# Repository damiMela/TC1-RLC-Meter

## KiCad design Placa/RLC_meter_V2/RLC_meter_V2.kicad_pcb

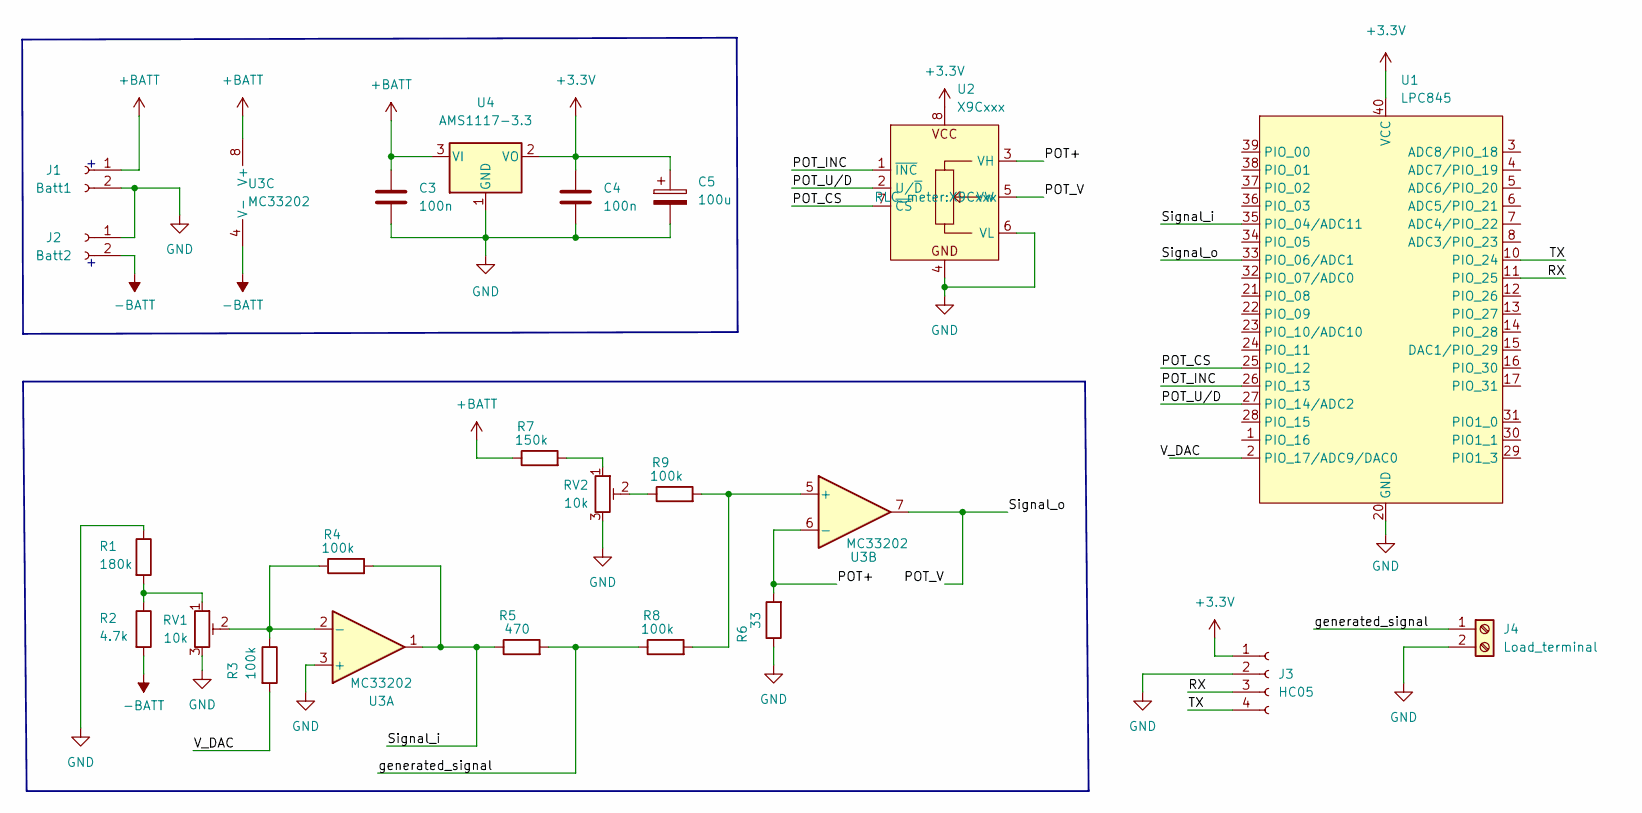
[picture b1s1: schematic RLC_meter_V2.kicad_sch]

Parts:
C3, C4: 100n; C_Disc_D5.0mm_W2.5mm_P2.50mm
C5: 100u; CP_Radial_D8.0mm_P5.00mm
J1: Batt1; PinHeader_1x02_P2.54mm_Vertical
J2: Batt2; PinHeader_1x02_P2.54mm_Vertical
J3: HC05; PinHeader_1x04_P2.54mm_Horizontal
J4: Load_terminal; TerminalBlock_Philmore_TB132_1x02_P5.00mm_Horizontal
R1: 180k; R_Axial_DIN0207_L6.3mm_D2.5mm_P15.24mm_Horizontal
R2: 4.7k; R_Axial_DIN0207_L6.3mm_D2.5mm_P15.24mm_Horizontal
R3, R4, R8, R9: 100k; R_Axial_DIN0207_L6.3mm_D2.5mm_P15.24mm_Horizontal
R5: 470; R_Axial_DIN0207_L6.3mm_D2.5mm_P15.24mm_Horizontal
R6: 33; R_Axial_DIN0207_L6.3mm_D2.5mm_P15.24mm_Horizontal
R7: 150k; R_Axial_DIN0207_L6.3mm_D2.5mm_P15.24mm_Horizontal
RV1, RV2: 10k; Potentiometer_Bourns_3386C_Horizontal
U1: LPC845
U2: X9Cxxx
U3: MC33202; DIP-8_W7.62mm_Socket_LongPads
U4: AMS1117-3.3; PinHeader_1x03_P2.54mm_Vertical

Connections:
+3.3V: C4.1, C5.1, J3.1, U1.40 (VCC), U2.8, U4.2 (VO)
+BATT: C3.1, J1.1, R7.1, U3.8 (V+), U4.3 (VI)
-BATT: J2.2, R2.2, U3.4 (V-)
/POT+: R6.2, U2.3 (VH), U3.6 (-)
/POT_CS: U1.25 (PIO_12), U2.7 (~CS)
/POT_INC: U1.26 (PIO_13), U2.1 (~INC)
/POT_U/D: U1.27 (PIO_14/ADC2), U2.2 (U/~D)
/POT_V: U1.33 (PIO_06/ADC1), U2.5 (VW), U3.7
/RX: J3.3, U1.11 (PIO_25)
/Signal_i: R4.2, R5.1, U1.35 (PIO_04/ADC11), U3.1
/TX: J3.4, U1.10 (PIO_24)
/V_DAC: R3.2, U1.2 (PIO_17/ADC9/DAC0)
/generated_signal: J4.1, R5.2, R8.1
GND: C3.2, C4.2, C5.2, J1.2, J2.1, J3.2, J4.2, R1.1, R6.1, RV1.3, RV2.3, U1.20 (GND), U2.4, U2.6 (VL), U3.3 (+), U4.1 (GND)
unnamed: R1.2, R2.1, RV1.1
unnamed: R3.1, R4.1, RV1.2, U3.2 (-)
unnamed: R7.2, RV2.1
unnamed: R9.1, RV2.2
unnamed: R8.2, R9.2, U3.5 (+)

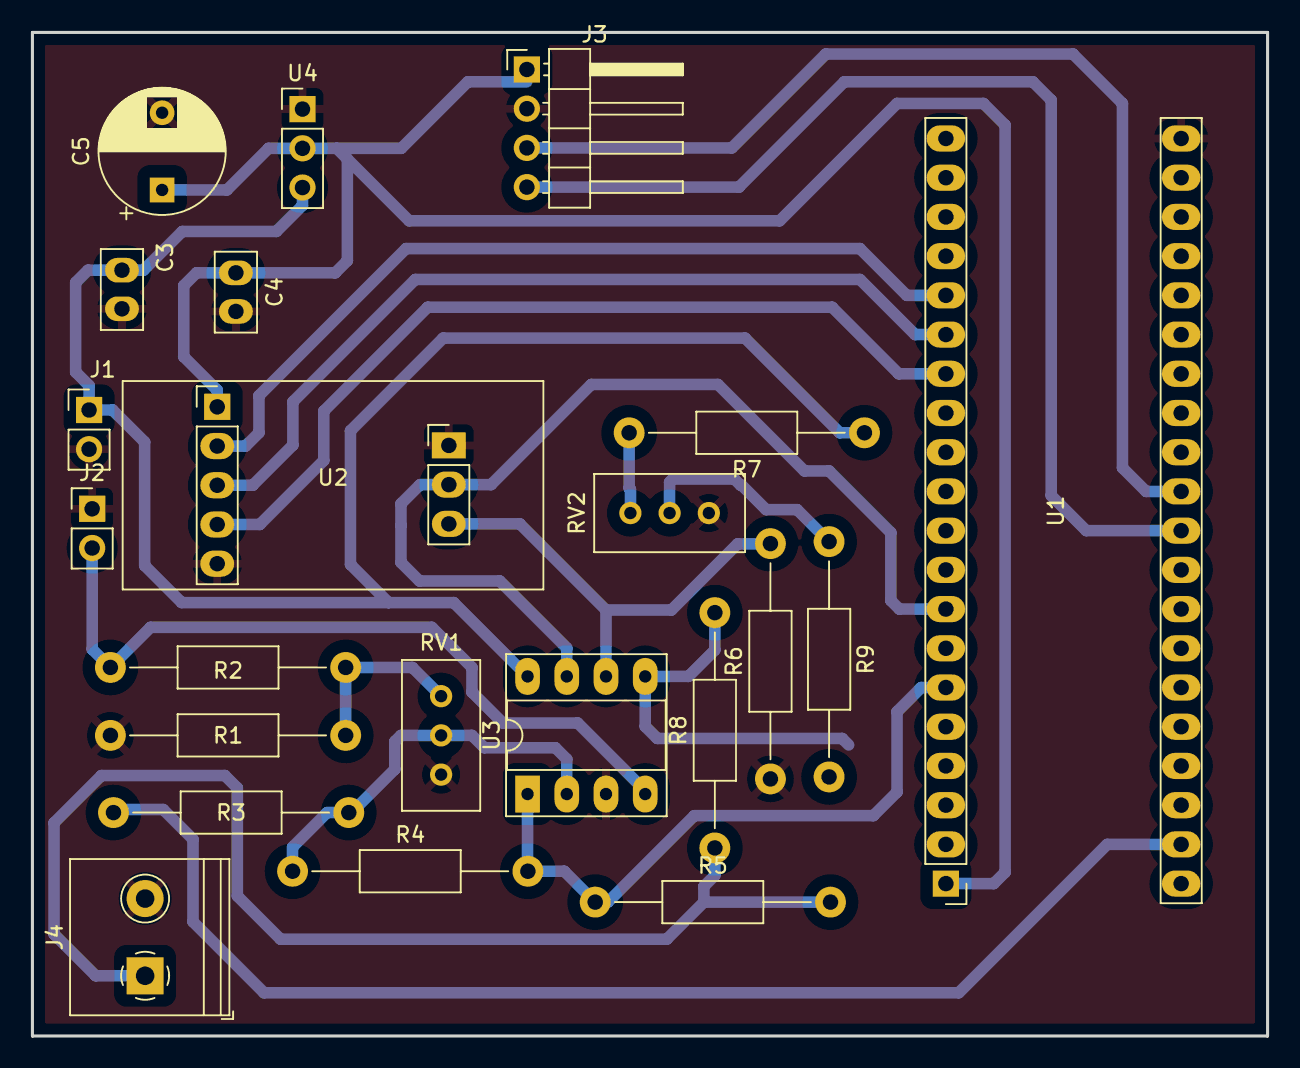
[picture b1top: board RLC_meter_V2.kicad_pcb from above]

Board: 2 copper layers, 80.0 x 65.0 mm, 22 parts (0 on the bottom side), 19 nets.

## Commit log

2022-07-22 simulaciones TINA
2022-07-22 NXP845 datasheets
2022-07-24 simulaciones con capacitor e inductor
2022-07-24 simulacion con capacitor modificada
2022-09-07 generador DAC
2022-09-07 script MATLAB para generar seno del DAC
2022-09-07 actualizo DAC
2022-09-07 modifico frecuencias de trabajo
2022-09-07 cambio script
2022-09-15 actualización de simulación y placa
2022-12-01 massive update. Local to git
2023-01-03 correxiones en clase
2023-01-12 fixed frecuency, single letter command, general revision
2023-01-17 update code
2023-01-18 code
2023-02-02 final commit
2023-02-16 last commit
